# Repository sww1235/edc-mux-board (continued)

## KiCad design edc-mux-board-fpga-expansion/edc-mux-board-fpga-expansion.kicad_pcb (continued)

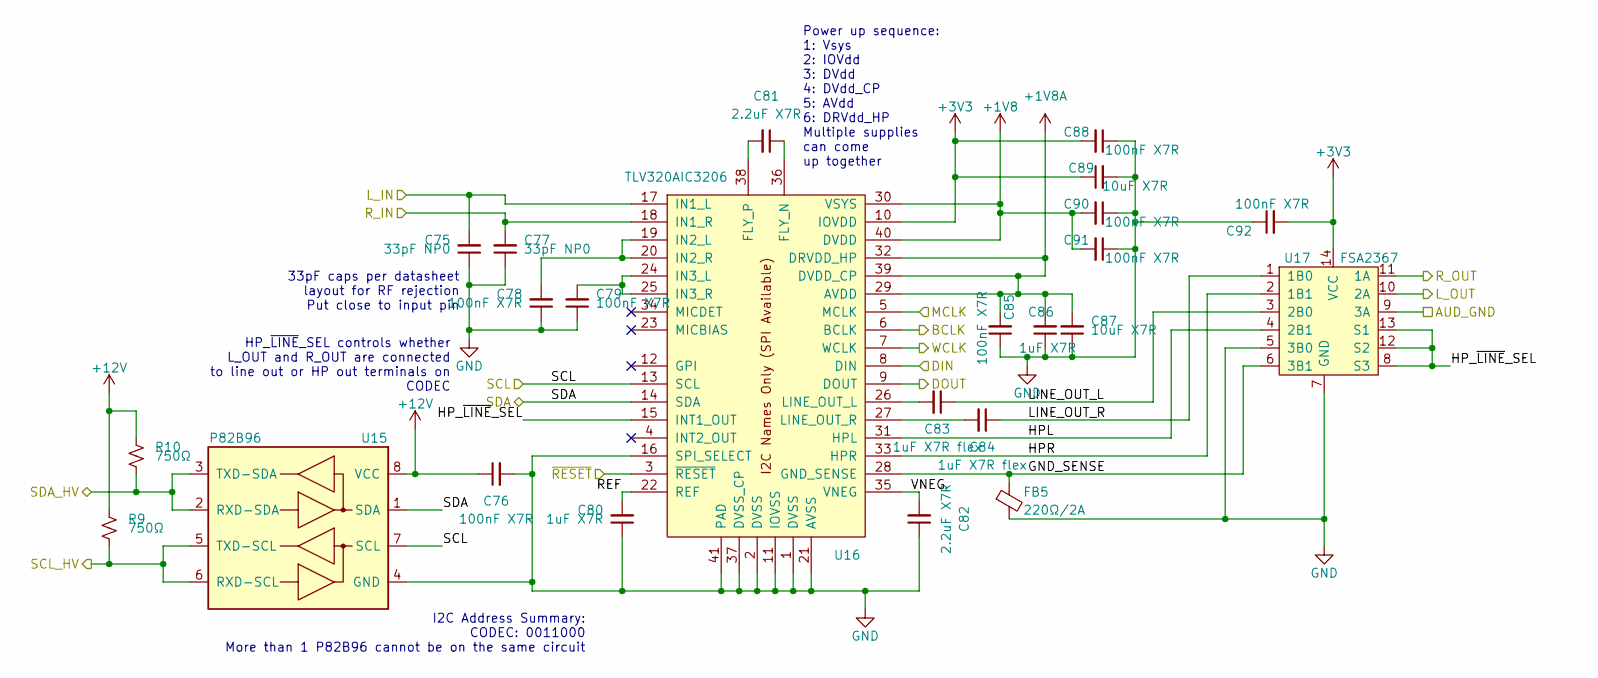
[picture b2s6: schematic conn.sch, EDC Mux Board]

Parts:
C3, C5: 33pF NP0; C_0402_1005Metric; Manufacturers Part Numb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 04023A330FAT2A
C4, C6, C7, C13, C16, C18, C19, C20: 100nF X7R; C_0603_1608Metric; Manufacturers Part Numb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 C0603C104J3RACAUTO
C8, C14: 1uF X7R; C_0603_1608Metric; Manufacturers Part Numb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 CGA3E1X7R1E105K080AC
C9, C10: 2.2uF X7R; C_0805_2012Metric; Manufacturers Part Numb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 CGA4J3X7R1E225K125AB
C11, C12: 1uF X7R flex; C_0805_2012Metric; Manufacturers Part Numb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 C0805X105J3RECAUTO
C15, C17: 10uF X7R; C_1206_3216Metric; Manufacturers Part Numb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 C1206C106J3RACAUTO
FB1: 220Ω/2A; L_0603_1608Metric; Manufacturers Part Numb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 MPZ1608S221A
R1, R2: 750Ω; R_0402_1005Metric
U3: P82B96; TSSOP-8_3x3mm_P0.65mm; Manufacturers Part Numb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 P82B96
U4: TLV320AIC3206; UQFN-40-1EP_5x5mm_P0.4mm_EP3.8x3.8mm_ThermalVias; Manufacturers Part Numb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 TLV320AIC3206
U5: FSA2367; TSSOP-14_4.4x5mm_P0.65mm; Manufacturers Part Numb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 FSA2367MTCX

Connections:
+1V8: C13.2, C14.2, C15.2, C18.2, C19.2, U4.29 (AVDD), U4.30 (VSYS), U4.32 (DRVDD_HP), U4.39 (DVDD_CP), U4.40 (DVDD); also elsewhere on the board
+3V3: C16.2, C17.1, C20.2, U4.10 (IOVDD), U5.14 (VCC); also elsewhere on the board
+12V: C4.1, R1.1, R2.1, U3.8 (VCC); also elsewhere on the board
/Bottom Side Connector Interconnects/BCLK8: U4.6 (BCLK); also elsewhere on the board
/Bottom Side Connector Interconnects/DIN8: U4.8 (DIN); also elsewhere on the board
/Bottom Side Connector Interconnects/DOUT8: U4.9 (DOUT); also elsewhere on the board
/Bottom Side Connector Interconnects/WCLK8: U4.7 (WCLK); also elsewhere on the board
/CODEC interconnection sheet/AUD_GND8: U5.9 (3A); also elsewhere on the board
/CODEC interconnection sheet/Interface - Connector 8/GND_SENSE: FB1.1, U4.28 (GND_SENSE), U5.6 (3B1)
/CODEC interconnection sheet/Interface - Connector 8/HPL: U4.31 (HPL), U5.4 (2B1)
/CODEC interconnection sheet/Interface - Connector 8/HPR: U4.33 (HPR), U5.2 (1B1)
/CODEC interconnection sheet/Interface - Connector 8/HP_~LINE~_SEL: U4.15 (INT1_OUT), U5.8 (S3), U5.12 (S2), U5.13 (S1)
/CODEC interconnection sheet/Interface - Connector 8/LINE_OUT_L: C11.1, U5.3 (2B0)
/CODEC interconnection sheet/Interface - Connector 8/LINE_OUT_R: C12.1, U5.1 (1B0)
/CODEC interconnection sheet/Interface - Connector 8/REF: C8.2, U4.22 (REF)
/CODEC interconnection sheet/Interface - Connector 8/VNEG: C10.2, U4.35 (VNEG)
/CODEC interconnection sheet/L_IN8: C3.2, U4.17 (IN1_L); also elsewhere on the board
/CODEC interconnection sheet/L_OUT8: U5.10 (2A); also elsewhere on the board
/CODEC interconnection sheet/MCLK8: U4.5 (MCLK); also elsewhere on the board
/CODEC interconnection sheet/R_IN8: C5.2, U4.18 (IN1_R); also elsewhere on the board
/CODEC interconnection sheet/R_OUT8: U5.11 (1A); also elsewhere on the board
/CODEC interconnection sheet/SCL8: U3.7 (SCL), U4.13 (SCL); also elsewhere on the board
/CODEC interconnection sheet/SCL_HV8: R1.2, U3.5 (TXD-SCL), U3.6 (RXD-SCL); also elsewhere on the board
/CODEC interconnection sheet/SDA8: U3.1 (SDA), U4.14 (SDA); also elsewhere on the board
/CODEC interconnection sheet/SDA_HV8: R2.2, U3.2 (RXD-SDA), U3.3 (TXD-SDA); also elsewhere on the board
/CODEC interconnection sheet/~RESET~8: U4.3 (~RESET); also elsewhere on the board
GND: C3.1, C4.2, C5.1, C6.1, C7.1, C8.1, C10.1, C13.1, C14.1, C15.1, C16.1, C17.2, C18.1, C19.1, C20.1, FB1.2, U3.4 (GND), U4.1 (DVSS), U4.2 (DVSS), U4.11 (IOVSS), U4.16 (SPI_SELECT), U4.21 (AVSS), U4.37 (DVSS_CP), U4.41 (PAD), U5.5 (3B0), U5.7 (GND); also elsewhere on the board
unnamed: C6.2, U4.19 (IN2_L), U4.20 (IN2_R)
unnamed: C7.2, U4.24 (IN3_L), U4.25 (IN3_R)
unnamed: C9.1, U4.36 (FLY_N)
unnamed: C9.2, U4.38 (FLY_P)
unnamed: C11.2, U4.26 (LINE_OUT_L)
unnamed: C12.2, U4.27 (LINE_OUT_R)

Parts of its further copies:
C21, C23, C39, C41, C57, C59, C75, C77, C93, C95, C111, C113, C129, C131: 33pF NP0; C_0402_1005Metric; Manufacturers Part Numb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 04023A330FAT2A
C22, C24, C25, C31, C34, C36, C37, C38, C40, C42, C43, C49, C52, C54, C55, C56, C58, C60, C61, C67, C70, C72, C73, C74, C76, C78, C79, C85, C88, C90, C91, C92, C94, C96, C97, C103, C106, C108, C109, C110, C112, C114, C115, C121, C124, C126, C127, C128, C130, C132, C133, C139, C142, C144, C145, C146: 100nF X7R; C_0603_1608Metric; Manufacturers Part Numb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 C0603C104J3RACAUTO
C26, C32, C44, C50, C62, C68, C80, C86, C98, C104, C116, C122, C134, C140: 1uF X7R; C_0603_1608Metric; Manufacturers Part Numb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 CGA3E1X7R1E105K080AC
C27, C28, C45, C46, C63, C64, C81, C82, C99, C100, C117, C118, C135, C136: 2.2uF X7R; C_0805_2012Metric; Manufacturers Part Numb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 CGA4J3X7R1E225K125AB
C29, C30, C47, C48, C65, C66, C83, C84, C101, C102, C119, C120, C137, C138: 1uF X7R flex; C_0805_2012Metric; Manufacturers Part Numb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 C0805X105J3RECAUTO
C33, C35, C51, C53, C69, C71, C87, C89, C105, C107, C123, C125, C141, C143: 10uF X7R; C_1206_3216Metric; Manufacturers Part Numb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 C1206C106J3RACAUTO
FB2, FB3, FB4, FB5, FB6, FB7, FB8: 220Ω/2A; L_0603_1608Metric; Manufacturers Part Numb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 MPZ1608S221A
R3, R4, R5, R6, R7, R8, R9, R10, R11, R12, R13, R14, R15, R16: 750Ω; R_0402_1005Metric
U6, U9, U12, U15, U18, U21, U24: P82B96; TSSOP-8_3x3mm_P0.65mm; Manufacturers Part Numb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 P82B96
U7, U10, U13, U16, U19, U22, U25: TLV320AIC3206; UQFN-40-1EP_5x5mm_P0.4mm_EP3.8x3.8mm_ThermalVias; Manufacturers Part Numb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 TLV320AIC3206
U8, U11, U14, U17, U20, U23, U26: FSA2367; TSSOP-14_4.4x5mm_P0.65mm; Manufacturers Part Numb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 FSA2367MTCX

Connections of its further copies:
+1V8: C31.2, C32.2, C33.2, C36.2, C37.2, C49.2, C50.2, C51.2, C54.2, C55.2, C67.2, C68.2, C69.2, C72.2, C73.2, C85.2, C86.2, C87.2, C90.2, C91.2, C103.2, C104.2, C105.2, C108.2, C109.2, C121.2, C122.2, C123.2, C126.2, C127.2, C139.2, C140.2, C141.2, C144.2, C145.2, U7.29 (AVDD), U7.30 (VSYS), U7.32 (DRVDD_HP), U7.39 (DVDD_CP), U7.40 (DVDD), U10.29 (AVDD), U10.30 (VSYS), U10.32 (DRVDD_HP), U10.39 (DVDD_CP), U10.40 (DVDD), U13.29 (AVDD), U13.30 (VSYS), U13.32 (DRVDD_HP), U13.39 (DVDD_CP), U13.40 (DVDD), U16.29 (AVDD), U16.30 (VSYS), U16.32 (DRVDD_HP), U16.39 (DVDD_CP), U16.40 (DVDD), U19.29 (AVDD), U19.30 (VSYS), U19.32 (DRVDD_HP), U19.39 (DVDD_CP), U19.40 (DVDD), U22.29 (AVDD), U22.30 (VSYS), U22.32 (DRVDD_HP), U22.39 (DVDD_CP), U22.40 (DVDD), U25.29 (AVDD), U25.30 (VSYS), U25.32 (DRVDD_HP), U25.39 (DVDD_CP), U25.40 (DVDD); also elsewhere on the board
+3V3: C34.2, C35.1, C38.2, C52.2, C53.1, C56.2, C70.2, C71.1, C74.2, C88.2, C89.1, C92.2, C106.2, C107.1, C110.2, C124.2, C125.1, C128.2, C142.2, C143.1, C146.2, U7.10 (IOVDD), U8.14 (VCC), U10.10 (IOVDD), U11.14 (VCC), U13.10 (IOVDD), U14.14 (VCC), U16.10 (IOVDD), U17.14 (VCC), U19.10 (IOVDD), U20.14 (VCC), U22.10 (IOVDD), U23.14 (VCC), U25.10 (IOVDD), U26.14 (VCC); also elsewhere on the board
+12V: C22.1, C40.1, C58.1, C76.1, C94.1, C112.1, C130.1, R3.1, R4.1, R5.1, R6.1, R7.1, R8.1, R9.1, R10.1, R11.1, R12.1, R13.1, R14.1, R15.1, R16.1, U6.8 (VCC), U9.8 (VCC), U12.8 (VCC), U15.8 (VCC), U18.8 (VCC), U21.8 (VCC), U24.8 (VCC); also elsewhere on the board
/Bottom Side Connector Interconnects/BCLK9: U7.6 (BCLK); also elsewhere on the board
/Bottom Side Connector Interconnects/BCLK10: U10.6 (BCLK); also elsewhere on the board
/Bottom Side Connector Interconnects/BCLK11: U13.6 (BCLK); also elsewhere on the board
/Bottom Side Connector Interconnects/BCLK12: U16.6 (BCLK); also elsewhere on the board
/Bottom Side Connector Interconnects/BCLK13: U19.6 (BCLK); also elsewhere on the board
/Bottom Side Connector Interconnects/BCLK14: U22.6 (BCLK); also elsewhere on the board
/Bottom Side Connector Interconnects/BCLK15: U25.6 (BCLK); also elsewhere on the board
/Bottom Side Connector Interconnects/DIN9: U7.8 (DIN); also elsewhere on the board
/Bottom Side Connector Interconnects/DIN10: U10.8 (DIN); also elsewhere on the board
/Bottom Side Connector Interconnects/DIN11: U13.8 (DIN); also elsewhere on the board
/Bottom Side Connector Interconnects/DIN12: U16.8 (DIN); also elsewhere on the board
/Bottom Side Connector Interconnects/DIN13: U19.8 (DIN); also elsewhere on the board
/Bottom Side Connector Interconnects/DIN14: U22.8 (DIN); also elsewhere on the board
/Bottom Side Connector Interconnects/DIN15: U25.8 (DIN); also elsewhere on the board
/Bottom Side Connector Interconnects/DOUT9: U7.9 (DOUT); also elsewhere on the board
/Bottom Side Connector Interconnects/DOUT10: U10.9 (DOUT); also elsewhere on the board
/Bottom Side Connector Interconnects/DOUT11: U13.9 (DOUT); also elsewhere on the board
/Bottom Side Connector Interconnects/DOUT12: U16.9 (DOUT); also elsewhere on the board
/Bottom Side Connector Interconnects/DOUT13: U19.9 (DOUT); also elsewhere on the board
/Bottom Side Connector Interconnects/DOUT14: U22.9 (DOUT); also elsewhere on the board
/Bottom Side Connector Interconnects/DOUT15: U25.9 (DOUT); also elsewhere on the board
/Bottom Side Connector Interconnects/WCLK9: U7.7 (WCLK); also elsewhere on the board
/Bottom Side Connector Interconnects/WCLK10: U10.7 (WCLK); also elsewhere on the board
/Bottom Side Connector Interconnects/WCLK11: U13.7 (WCLK); also elsewhere on the board
/Bottom Side Connector Interconnects/WCLK12: U16.7 (WCLK); also elsewhere on the board
/Bottom Side Connector Interconnects/WCLK13: U19.7 (WCLK); also elsewhere on the board
/Bottom Side Connector Interconnects/WCLK14: U22.7 (WCLK); also elsewhere on the board
/Bottom Side Connector Interconnects/WCLK15: U25.7 (WCLK); also elsewhere on the board
/CODEC interconnection sheet/AUD_GND9: U8.9 (3A); also elsewhere on the board
/CODEC interconnection sheet/AUD_GND10: U11.9 (3A); also elsewhere on the board
/CODEC interconnection sheet/AUD_GND11: U14.9 (3A); also elsewhere on the board
/CODEC interconnection sheet/AUD_GND12: U17.9 (3A); also elsewhere on the board
/CODEC interconnection sheet/AUD_GND13: U20.9 (3A); also elsewhere on the board
/CODEC interconnection sheet/AUD_GND14: U23.9 (3A); also elsewhere on the board
/CODEC interconnection sheet/AUD_GND15: U26.9 (3A); also elsewhere on the board
/CODEC interconnection sheet/Interface - Connector 9/GND_SENSE: FB2.1, U7.28 (GND_SENSE), U8.6 (3B1)
/CODEC interconnection sheet/Interface - Connector 9/HPL: U7.31 (HPL), U8.4 (2B1)
/CODEC interconnection sheet/Interface - Connector 9/HPR: U7.33 (HPR), U8.2 (1B1)
/CODEC interconnection sheet/Interface - Connector 9/HP_~LINE~_SEL: U7.15 (INT1_OUT), U8.8 (S3), U8.12 (S2), U8.13 (S1)
/CODEC interconnection sheet/Interface - Connector 9/LINE_OUT_L: C29.1, U8.3 (2B0)
/CODEC interconnection sheet/Interface - Connector 9/LINE_OUT_R: C30.1, U8.1 (1B0)
/CODEC interconnection sheet/Interface - Connector 9/REF: C26.2, U7.22 (REF)
/CODEC interconnection sheet/Interface - Connector 9/VNEG: C28.2, U7.35 (VNEG)
/CODEC interconnection sheet/Interface - Connector 10/GND_SENSE: FB3.1, U10.28 (GND_SENSE), U11.6 (3B1)
/CODEC interconnection sheet/Interface - Connector 10/HPL: U10.31 (HPL), U11.4 (2B1)
/CODEC interconnection sheet/Interface - Connector 10/HPR: U10.33 (HPR), U11.2 (1B1)
/CODEC interconnection sheet/Interface - Connector 10/HP_~LINE~_SEL: U10.15 (INT1_OUT), U11.8 (S3), U11.12 (S2), U11.13 (S1)
/CODEC interconnection sheet/Interface - Connector 10/LINE_OUT_L: C47.1, U11.3 (2B0)
/CODEC interconnection sheet/Interface - Connector 10/LINE_OUT_R: C48.1, U11.1 (1B0)
/CODEC interconnection sheet/Interface - Connector 10/REF: C44.2, U10.22 (REF)
/CODEC interconnection sheet/Interface - Connector 10/VNEG: C46.2, U10.35 (VNEG)
/CODEC interconnection sheet/Interface - Connector 11/GND_SENSE: FB4.1, U13.28 (GND_SENSE), U14.6 (3B1)
/CODEC interconnection sheet/Interface - Connector 11/HPL: U13.31 (HPL), U14.4 (2B1)
/CODEC interconnection sheet/Interface - Connector 11/HPR: U13.33 (HPR), U14.2 (1B1)
/CODEC interconnection sheet/Interface - Connector 11/HP_~LINE~_SEL: U13.15 (INT1_OUT), U14.8 (S3), U14.12 (S2), U14.13 (S1)
/CODEC interconnection sheet/Interface - Connector 11/LINE_OUT_L: C65.1, U14.3 (2B0)
/CODEC interconnection sheet/Interface - Connector 11/LINE_OUT_R: C66.1, U14.1 (1B0)
/CODEC interconnection sheet/Interface - Connector 11/REF: C62.2, U13.22 (REF)
/CODEC interconnection sheet/Interface - Connector 11/VNEG: C64.2, U13.35 (VNEG)
/CODEC interconnection sheet/Interface - Connector 12/GND_SENSE: FB5.1, U16.28 (GND_SENSE), U17.6 (3B1)
/CODEC interconnection sheet/Interface - Connector 12/HPL: U16.31 (HPL), U17.4 (2B1)
/CODEC interconnection sheet/Interface - Connector 12/HPR: U16.33 (HPR), U17.2 (1B1)
/CODEC interconnection sheet/Interface - Connector 12/HP_~LINE~_SEL: U16.15 (INT1_OUT), U17.8 (S3), U17.12 (S2), U17.13 (S1)
/CODEC interconnection sheet/Interface - Connector 12/LINE_OUT_L: C83.1, U17.3 (2B0)
/CODEC interconnection sheet/Interface - Connector 12/LINE_OUT_R: C84.1, U17.1 (1B0)
/CODEC interconnection sheet/Interface - Connector 12/REF: C80.2, U16.22 (REF)
/CODEC interconnection sheet/Interface - Connector 12/VNEG: C82.2, U16.35 (VNEG)
/CODEC interconnection sheet/Interface - Connector 13/GND_SENSE: FB6.1, U19.28 (GND_SENSE), U20.6 (3B1)
/CODEC interconnection sheet/Interface - Connector 13/HPL: U19.31 (HPL), U20.4 (2B1)
/CODEC interconnection sheet/Interface - Connector 13/HPR: U19.33 (HPR), U20.2 (1B1)
/CODEC interconnection sheet/Interface - Connector 13/HP_~LINE~_SEL: U19.15 (INT1_OUT), U20.8 (S3), U20.12 (S2), U20.13 (S1)
/CODEC interconnection sheet/Interface - Connector 13/LINE_OUT_L: C101.1, U20.3 (2B0)
/CODEC interconnection sheet/Interface - Connector 13/LINE_OUT_R: C102.1, U20.1 (1B0)
/CODEC interconnection sheet/Interface - Connector 13/REF: C98.2, U19.22 (REF)
/CODEC interconnection sheet/Interface - Connector 13/VNEG: C100.2, U19.35 (VNEG)
/CODEC interconnection sheet/Interface - Connector 14/GND_SENSE: FB7.1, U22.28 (GND_SENSE), U23.6 (3B1)
/CODEC interconnection sheet/Interface - Connector 14/HPL: U22.31 (HPL), U23.4 (2B1)
/CODEC interconnection sheet/Interface - Connector 14/HPR: U22.33 (HPR), U23.2 (1B1)
/CODEC interconnection sheet/Interface - Connector 14/HP_~LINE~_SEL: U22.15 (INT1_OUT), U23.8 (S3), U23.12 (S2), U23.13 (S1)
/CODEC interconnection sheet/Interface - Connector 14/LINE_OUT_L: C119.1, U23.3 (2B0)
/CODEC interconnection sheet/Interface - Connector 14/LINE_OUT_R: C120.1, U23.1 (1B0)
/CODEC interconnection sheet/Interface - Connector 14/REF: C116.2, U22.22 (REF)
/CODEC interconnection sheet/Interface - Connector 14/VNEG: C118.2, U22.35 (VNEG)
/CODEC interconnection sheet/Interface - Connector 15/GND_SENSE: FB8.1, U25.28 (GND_SENSE), U26.6 (3B1)
/CODEC interconnection sheet/Interface - Connector 15/HPL: U25.31 (HPL), U26.4 (2B1)
/CODEC interconnection sheet/Interface - Connector 15/HPR: U25.33 (HPR), U26.2 (1B1)
/CODEC interconnection sheet/Interface - Connector 15/HP_~LINE~_SEL: U25.15 (INT1_OUT), U26.8 (S3), U26.12 (S2), U26.13 (S1)
/CODEC interconnection sheet/Interface - Connector 15/LINE_OUT_L: C137.1, U26.3 (2B0)
/CODEC interconnection sheet/Interface - Connector 15/LINE_OUT_R: C138.1, U26.1 (1B0)
/CODEC interconnection sheet/Interface - Connector 15/REF: C134.2, U25.22 (REF)
/CODEC interconnection sheet/Interface - Connector 15/VNEG: C136.2, U25.35 (VNEG)
/CODEC interconnection sheet/L_IN9: C21.2, U7.17 (IN1_L); also elsewhere on the board
/CODEC interconnection sheet/L_IN10: C39.2, U10.17 (IN1_L); also elsewhere on the board
/CODEC interconnection sheet/L_IN11: C57.2, U13.17 (IN1_L); also elsewhere on the board
/CODEC interconnection sheet/L_IN12: C75.2, U16.17 (IN1_L); also elsewhere on the board
/CODEC interconnection sheet/L_IN13: C93.2, U19.17 (IN1_L); also elsewhere on the board
/CODEC interconnection sheet/L_IN14: C111.2, U22.17 (IN1_L); also elsewhere on the board
/CODEC interconnection sheet/L_IN15: C129.2, U25.17 (IN1_L); also elsewhere on the board
/CODEC interconnection sheet/L_OUT9: U8.10 (2A); also elsewhere on the board
/CODEC interconnection sheet/L_OUT10: U11.10 (2A); also elsewhere on the board
/CODEC interconnection sheet/L_OUT11: U14.10 (2A); also elsewhere on the board
/CODEC interconnection sheet/L_OUT12: U17.10 (2A); also elsewhere on the board
/CODEC interconnection sheet/L_OUT13: U20.10 (2A); also elsewhere on the board
/CODEC interconnection sheet/L_OUT14: U23.10 (2A); also elsewhere on the board
/CODEC interconnection sheet/L_OUT15: U26.10 (2A); also elsewhere on the board
/CODEC interconnection sheet/MCLK9: U7.5 (MCLK); also elsewhere on the board
/CODEC interconnection sheet/MCLK10: U10.5 (MCLK); also elsewhere on the board
/CODEC interconnection sheet/MCLK11: U13.5 (MCLK); also elsewhere on the board
/CODEC interconnection sheet/MCLK12: U16.5 (MCLK); also elsewhere on the board
/CODEC interconnection sheet/MCLK13: U19.5 (MCLK); also elsewhere on the board
/CODEC interconnection sheet/MCLK14: U22.5 (MCLK); also elsewhere on the board
/CODEC interconnection sheet/MCLK15: U25.5 (MCLK); also elsewhere on the board
/CODEC interconnection sheet/R_IN9: C23.2, U7.18 (IN1_R); also elsewhere on the board
/CODEC interconnection sheet/R_IN10: C41.2, U10.18 (IN1_R); also elsewhere on the board
/CODEC interconnection sheet/R_IN11: C59.2, U13.18 (IN1_R); also elsewhere on the board
/CODEC interconnection sheet/R_IN12: C77.2, U16.18 (IN1_R); also elsewhere on the board
/CODEC interconnection sheet/R_IN13: C95.2, U19.18 (IN1_R); also elsewhere on the board
/CODEC interconnection sheet/R_IN14: C113.2, U22.18 (IN1_R); also elsewhere on the board
/CODEC interconnection sheet/R_IN15: C131.2, U25.18 (IN1_R); also elsewhere on the board
/CODEC interconnection sheet/R_OUT9: U8.11 (1A); also elsewhere on the board
/CODEC interconnection sheet/R_OUT10: U11.11 (1A); also elsewhere on the board
/CODEC interconnection sheet/R_OUT11: U14.11 (1A); also elsewhere on the board
/CODEC interconnection sheet/R_OUT12: U17.11 (1A); also elsewhere on the board
/CODEC interconnection sheet/R_OUT13: U20.11 (1A); also elsewhere on the board
/CODEC interconnection sheet/R_OUT14: U23.11 (1A); also elsewhere on the board
/CODEC interconnection sheet/R_OUT15: U26.11 (1A); also elsewhere on the board
/CODEC interconnection sheet/SCL9: U6.7 (SCL), U7.13 (SCL); also elsewhere on the board
/CODEC interconnection sheet/SCL10: U9.7 (SCL), U10.13 (SCL); also elsewhere on the board
/CODEC interconnection sheet/SCL11: U12.7 (SCL), U13.13 (SCL); also elsewhere on the board
/CODEC interconnection sheet/SCL12: U15.7 (SCL), U16.13 (SCL); also elsewhere on the board
/CODEC interconnection sheet/SCL13: U18.7 (SCL), U19.13 (SCL); also elsewhere on the board
/CODEC interconnection sheet/SCL14: U21.7 (SCL), U22.13 (SCL); also elsewhere on the board
/CODEC interconnection sheet/SCL15: U24.7 (SCL), U25.13 (SCL); also elsewhere on the board
/CODEC interconnection sheet/SCL_HV9: R3.2, U6.5 (TXD-SCL), U6.6 (RXD-SCL); also elsewhere on the board
/CODEC interconnection sheet/SCL_HV10: R5.2, U9.5 (TXD-SCL), U9.6 (RXD-SCL); also elsewhere on the board
/CODEC interconnection sheet/SCL_HV11: R7.2, U12.5 (TXD-SCL), U12.6 (RXD-SCL); also elsewhere on the board
/CODEC interconnection sheet/SCL_HV12: R9.2, U15.5 (TXD-SCL), U15.6 (RXD-SCL); also elsewhere on the board
/CODEC interconnection sheet/SCL_HV13: R11.2, U18.5 (TXD-SCL), U18.6 (RXD-SCL); also elsewhere on the board
/CODEC interconnection sheet/SCL_HV14: R13.2, U21.5 (TXD-SCL), U21.6 (RXD-SCL); also elsewhere on the board
/CODEC interconnection sheet/SCL_HV15: R15.2, U24.5 (TXD-SCL), U24.6 (RXD-SCL); also elsewhere on the board
/CODEC interconnection sheet/SDA9: U6.1 (SDA), U7.14 (SDA); also elsewhere on the board
/CODEC interconnection sheet/SDA10: U9.1 (SDA), U10.14 (SDA); also elsewhere on the board
/CODEC interconnection sheet/SDA11: U12.1 (SDA), U13.14 (SDA); also elsewhere on the board
/CODEC interconnection sheet/SDA12: U15.1 (SDA), U16.14 (SDA); also elsewhere on the board
/CODEC interconnection sheet/SDA13: U18.1 (SDA), U19.14 (SDA); also elsewhere on the board
/CODEC interconnection sheet/SDA14: U21.1 (SDA), U22.14 (SDA); also elsewhere on the board
/CODEC interconnection sheet/SDA15: U24.1 (SDA), U25.14 (SDA); also elsewhere on the board
/CODEC interconnection sheet/SDA_HV9: R4.2, U6.2 (RXD-SDA), U6.3 (TXD-SDA); also elsewhere on the board
/CODEC interconnection sheet/SDA_HV10: R6.2, U9.2 (RXD-SDA), U9.3 (TXD-SDA); also elsewhere on the board
/CODEC interconnection sheet/SDA_HV11: R8.2, U12.2 (RXD-SDA), U12.3 (TXD-SDA); also elsewhere on the board
/CODEC interconnection sheet/SDA_HV12: R10.2, U15.2 (RXD-SDA), U15.3 (TXD-SDA); also elsewhere on the board
/CODEC interconnection sheet/SDA_HV13: R12.2, U18.2 (RXD-SDA), U18.3 (TXD-SDA); also elsewhere on the board
/CODEC interconnection sheet/SDA_HV14: R14.2, U21.2 (RXD-SDA), U21.3 (TXD-SDA); also elsewhere on the board
/CODEC interconnection sheet/SDA_HV15: R16.2, U24.2 (RXD-SDA), U24.3 (TXD-SDA); also elsewhere on the board
/CODEC interconnection sheet/~RESET~9: U7.3 (~RESET); also elsewhere on the board
/CODEC interconnection sheet/~RESET~10: U10.3 (~RESET); also elsewhere on the board
/CODEC interconnection sheet/~RESET~11: U13.3 (~RESET); also elsewhere on the board
/CODEC interconnection sheet/~RESET~12: U16.3 (~RESET); also elsewhere on the board
/CODEC interconnection sheet/~RESET~13: U19.3 (~RESET); also elsewhere on the board
/CODEC interconnection sheet/~RESET~14: U22.3 (~RESET); also elsewhere on the board
/CODEC interconnection sheet/~RESET~15: U25.3 (~RESET); also elsewhere on the board
GND: C21.1, C22.2, C23.1, C24.1, C25.1, C26.1, C28.1, C31.1, C32.1, C33.1, C34.1, C35.2, C36.1, C37.1, C38.1, C39.1, C40.2, C41.1, C42.1, C43.1, C44.1, C46.1, C49.1, C50.1, C51.1, C52.1, C53.2, C54.1, C55.1, C56.1, C57.1, C58.2, C59.1, C60.1, C61.1, C62.1, C64.1, C67.1, C68.1, C69.1, C70.1, C71.2, C72.1, C73.1, C74.1, C75.1, C76.2, C77.1, C78.1, C79.1, C80.1, C82.1, C85.1, C86.1, C87.1, C88.1, C89.2, C90.1, C91.1, C92.1, C93.1, C94.2, C95.1, C96.1, C97.1, C98.1, C100.1, C103.1, C104.1, C105.1, C106.1, C107.2, C108.1, C109.1, C110.1, C111.1, C112.2, C113.1, C114.1, C115.1, C116.1, C118.1, C121.1, C122.1, C123.1, C124.1, C125.2, C126.1, C127.1, C128.1, C129.1, C130.2, C131.1, C132.1, C133.1, C134.1, C136.1, C139.1, C140.1, C141.1, C142.1, C143.2, C144.1, C145.1, C146.1, FB2.2, FB3.2, FB4.2, FB5.2, FB6.2, FB7.2, FB8.2, U6.4 (GND), U7.1 (DVSS), U7.2 (DVSS), U7.11 (IOVSS), U7.16 (SPI_SELECT), U7.21 (AVSS), U7.37 (DVSS_CP), U7.41 (PAD), U8.5 (3B0), U8.7 (GND), U9.4 (GND), U10.1 (DVSS), U10.2 (DVSS), U10.11 (IOVSS), U10.16 (SPI_SELECT), U10.21 (AVSS), U10.37 (DVSS_CP), U10.41 (PAD), U11.5 (3B0), U11.7 (GND), U12.4 (GND), U13.1 (DVSS), U13.2 (DVSS), U13.11 (IOVSS), U13.16 (SPI_SELECT), U13.21 (AVSS), U13.37 (DVSS_CP), U13.41 (PAD), U14.5 (3B0), U14.7 (GND), U15.4 (GND), U16.1 (DVSS), U16.2 (DVSS), U16.11 (IOVSS), U16.16 (SPI_SELECT), U16.21 (AVSS), U16.37 (DVSS_CP), U16.41 (PAD), U17.5 (3B0), U17.7 (GND), U18.4 (GND), U19.1 (DVSS), U19.2 (DVSS), U19.11 (IOVSS), U19.16 (SPI_SELECT), U19.21 (AVSS), U19.37 (DVSS_CP), U19.41 (PAD), U20.5 (3B0), U20.7 (GND), U21.4 (GND), U22.1 (DVSS), U22.2 (DVSS), U22.11 (IOVSS), U22.16 (SPI_SELECT), U22.21 (AVSS), U22.37 (DVSS_CP), U22.41 (PAD), U23.5 (3B0), U23.7 (GND), U24.4 (GND), U25.1 (DVSS), U25.2 (DVSS), U25.11 (IOVSS), U25.16 (SPI_SELECT), U25.21 (AVSS), U25.37 (DVSS_CP), U25.41 (PAD), U26.5 (3B0), U26.7 (GND); also elsewhere on the board
unnamed: C24.2, U7.19 (IN2_L), U7.20 (IN2_R)
unnamed: C25.2, U7.24 (IN3_L), U7.25 (IN3_R)
unnamed: C27.1, U7.36 (FLY_N)
unnamed: C27.2, U7.38 (FLY_P)
unnamed: C29.2, U7.26 (LINE_OUT_L)
unnamed: C30.2, U7.27 (LINE_OUT_R)
unnamed: C42.2, U10.19 (IN2_L), U10.20 (IN2_R)
unnamed: C43.2, U10.24 (IN3_L), U10.25 (IN3_R)
unnamed: C45.1, U10.36 (FLY_N)
unnamed: C45.2, U10.38 (FLY_P)
unnamed: C47.2, U10.26 (LINE_OUT_L)
unnamed: C48.2, U10.27 (LINE_OUT_R)
unnamed: C60.2, U13.19 (IN2_L), U13.20 (IN2_R)
unnamed: C61.2, U13.24 (IN3_L), U13.25 (IN3_R)
unnamed: C63.1, U13.36 (FLY_N)
unnamed: C63.2, U13.38 (FLY_P)
unnamed: C65.2, U13.26 (LINE_OUT_L)
unnamed: C66.2, U13.27 (LINE_OUT_R)
unnamed: C78.2, U16.19 (IN2_L), U16.20 (IN2_R)
unnamed: C79.2, U16.24 (IN3_L), U16.25 (IN3_R)
unnamed: C81.1, U16.36 (FLY_N)
unnamed: C81.2, U16.38 (FLY_P)
unnamed: C83.2, U16.26 (LINE_OUT_L)
unnamed: C84.2, U16.27 (LINE_OUT_R)
unnamed: C96.2, U19.19 (IN2_L), U19.20 (IN2_R)
unnamed: C97.2, U19.24 (IN3_L), U19.25 (IN3_R)
unnamed: C99.1, U19.36 (FLY_N)
unnamed: C99.2, U19.38 (FLY_P)
unnamed: C101.2, U19.26 (LINE_OUT_L)
unnamed: C102.2, U19.27 (LINE_OUT_R)
unnamed: C114.2, U22.19 (IN2_L), U22.20 (IN2_R)
unnamed: C115.2, U22.24 (IN3_L), U22.25 (IN3_R)
unnamed: C117.1, U22.36 (FLY_N)
unnamed: C117.2, U22.38 (FLY_P)
unnamed: C119.2, U22.26 (LINE_OUT_L)
unnamed: C120.2, U22.27 (LINE_OUT_R)
unnamed: C132.2, U25.19 (IN2_L), U25.20 (IN2_R)
unnamed: C133.2, U25.24 (IN3_L), U25.25 (IN3_R)
unnamed: C135.1, U25.36 (FLY_N)
unnamed: C135.2, U25.38 (FLY_P)
unnamed: C137.2, U25.26 (LINE_OUT_L)
unnamed: C138.2, U25.27 (LINE_OUT_R)

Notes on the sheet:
33pF caps per datasheet layout for RF rejection Put close to input pin
Power up sequence: 1: Vsys 2: IOVdd 3: DVdd 4: DVdd_CP 5: AVdd 6: DRVdd_HP Multiple supplies can come up together
HP_~LINE~_SEL controls whether L_OUT and R_OUT are connected to line out or HP out terminals on CODEC
I2C Address Summary: CODEC: 0011000 More than 1 P82B96 cannot be on the same circuit

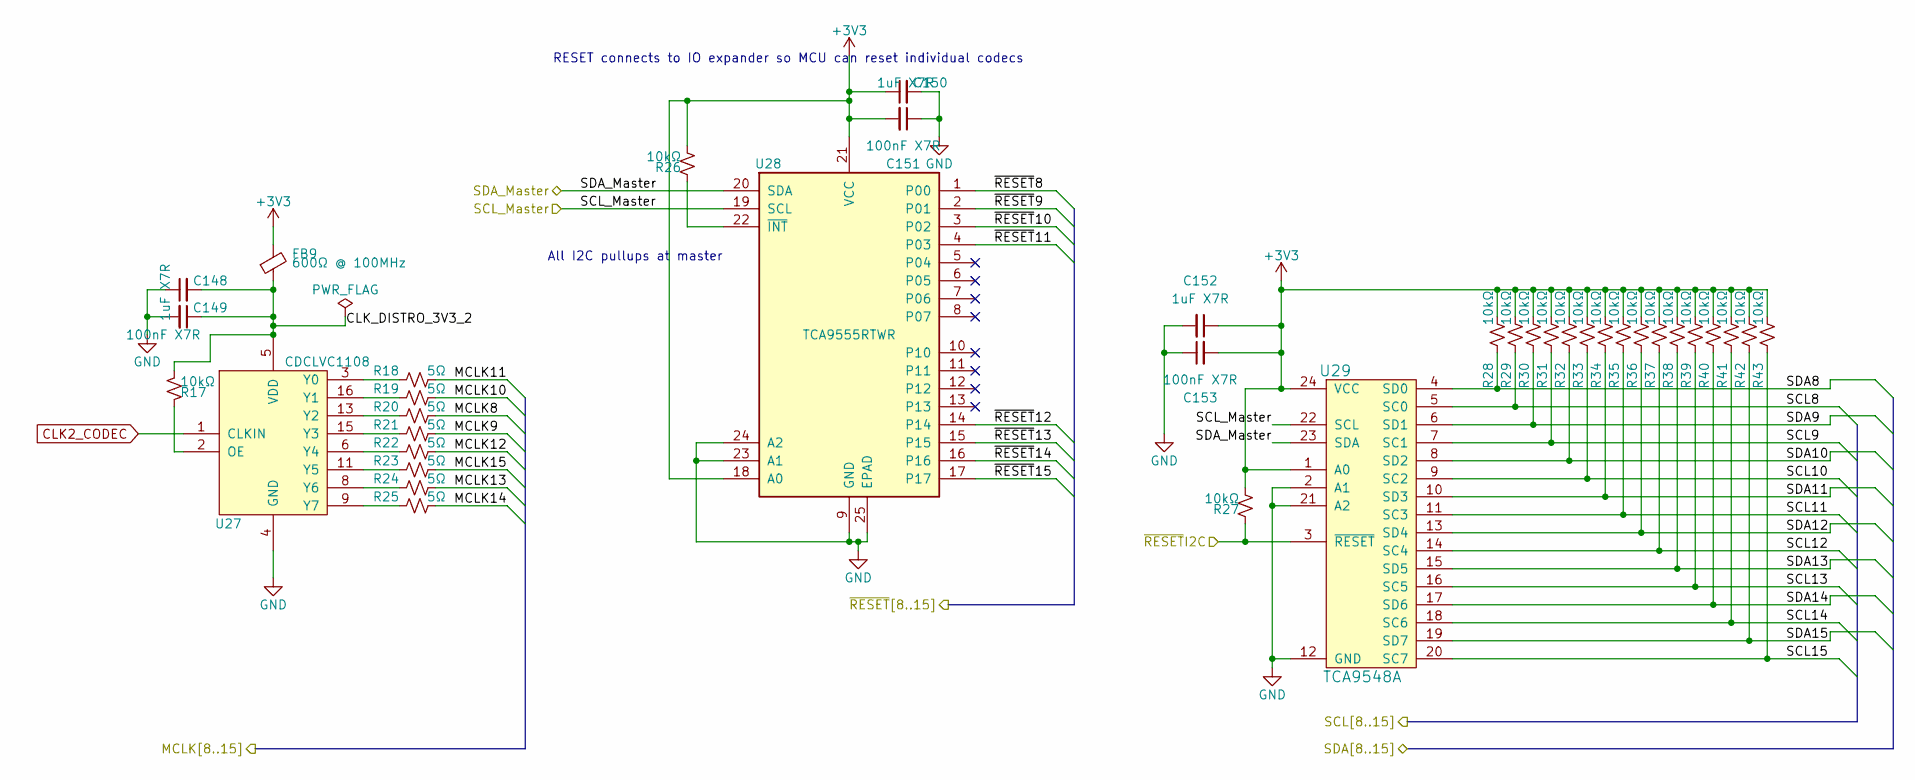
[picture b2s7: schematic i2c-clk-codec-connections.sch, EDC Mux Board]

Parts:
C148, C150, C152: 1uF X7R; C_0603_1608Metric; Manufacturers Part Numb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 CGA3E1X7R1E105K080AC
C149, C151, C153: 100nF X7R; C_0603_1608Metric; Manufacturers Part Numb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 C0603C104J3RACAUTO
FB9: 600Ω @ 100MHz; L_0805_2012Metric; Manufacturers Part Numb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 BLM21AG601SZ1D
R17, R26, R27, R28, R29, R30, R31, R32, R33, R34, R35, R36, R37, R38, R39, R40, R41, R42, R43: 10kΩ; R_0402_1005Metric
R18, R19, R20, R21, R22, R23, R24, R25: 5Ω; R_0402_1005Metric
U27: CDCLVC1108; TSSOP-16_4.4x5mm_P0.65mm; Manufacturers Part Numb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 CDCLVC1108
U28: TCA9555RTWR; QFN-24-1EP_4x4mm_P0.5mm_EP2.6x2.6mm_ThermalVias; Manufacturers Part Numb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 TCA9555
U29: TCA9548A; TSSOP-24_4.4x7.8mm_P0.65mm; Manufacturers Part Numb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 TCA9548

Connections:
+3V3: C150.1, C151.2, C152.1, C153.2, FB9.2, R26.2, R27.2, R28.2, R29.2, R30.2, R31.2, R32.2, R33.2, R34.2, R35.2, R36.2, R37.2, R38.2, R39.2, R40.2, R41.2, R42.2, R43.2, U28.18 (A0), U28.21 (VCC), U29.1 (A0), U29.24 (VCC); also elsewhere on the board
/CODEC interconnection sheet/Connections for MCLK and I2C Multiplexed Lines/CLK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: C148.2, C149.1, FB9.1, R17.2, U27.5 (VDD), U27.10 (VDD), U27.14 (VDD)
/CODEC interconnection sheet/MCLK8: R20.1; also elsewhere on the board
/CODEC interconnection sheet/MCLK9: R21.1; also elsewhere on the board
/CODEC interconnection sheet/MCLK10: R19.1; also elsewhere on the board
/CODEC interconnection sheet/MCLK11: R18.1; also elsewhere on the board
/CODEC interconnection sheet/MCLK12: R22.1; also elsewhere on the board
/CODEC interconnection sheet/MCLK13: R24.1; also elsewhere on the board
/CODEC interconnection sheet/MCLK14: R25.1; also elsewhere on the board
/CODEC interconnection sheet/MCLK15: R23.1; also elsewhere on the board
/CODEC interconnection sheet/SCL8: R29.1, U29.5 (SC0); also elsewhere on the board
/CODEC interconnection sheet/SCL9: R31.1, U29.7 (SC1); also elsewhere on the board
/CODEC interconnection sheet/SCL10: R33.1, U29.9 (SC2); also elsewhere on the board
/CODEC interconnection sheet/SCL11: R35.1, U29.11 (SC3); also elsewhere on the board
/CODEC interconnection sheet/SCL12: R37.1, U29.14 (SC4); also elsewhere on the board
/CODEC interconnection sheet/SCL13: R39.1, U29.16 (SC5); also elsewhere on the board
/CODEC interconnection sheet/SCL14: R41.1, U29.18 (SC6); also elsewhere on the board
/CODEC interconnection sheet/SCL15: R43.1, U29.20 (SC7); also elsewhere on the board
/CODEC interconnection sheet/SDA8: R28.1, U29.4 (SD0); also elsewhere on the board
/CODEC interconnection sheet/SDA9: R30.1, U29.6 (SD1); also elsewhere on the board
/CODEC interconnection sheet/SDA10: R32.1, U29.8 (SD2); also elsewhere on the board
/CODEC interconnection sheet/SDA11: R34.1, U29.10 (SD3); also elsewhere on the board
/CODEC interconnection sheet/SDA12: R36.1, U29.13 (SD4); also elsewhere on the board
/CODEC interconnection sheet/SDA13: R38.1, U29.15 (SD5); also elsewhere on the board
/CODEC interconnection sheet/SDA14: R40.1, U29.17 (SD6); also elsewhere on the board
/CODEC interconnection sheet/SDA15: R42.1, U29.19 (SD7); also elsewhere on the board
/CODEC interconnection sheet/~RESET~8: U28.1 (P00); also elsewhere on the board
/CODEC interconnection sheet/~RESET~9: U28.2 (P01); also elsewhere on the board
/CODEC interconnection sheet/~RESET~10: U28.3 (P02); also elsewhere on the board
/CODEC interconnection sheet/~RESET~11: U28.4 (P03); also elsewhere on the board
/CODEC interconnection sheet/~RESET~12: U28.14; also elsewhere on the board
/CODEC interconnection sheet/~RESET~13: U28.15; also elsewhere on the board
/CODEC interconnection sheet/~RESET~14: U28.16; also elsewhere on the board
/CODEC interconnection sheet/~RESET~15: U28.17; also elsewhere on the board
/SCL: U28.19 (SCL), U29.22 (SCL); also elsewhere on the board
/SDA: U28.20 (SDA), U29.23 (SDA); also elsewhere on the board
/~RESET~I2C: R27.1, U29.3 (~RESET); also elsewhere on the board
CLK2_CODEC: U27.1 (CLKIN); also elsewhere on the board
GND: C148.1, C149.2, C150.2, C151.1, C152.2, C153.1, U27.4 (GND), U27.7 (GND), U27.12 (GND), U28.9 (GND), U28.23 (A1), U28.24 (A2), U28.25 (EPAD), U29.2 (A1), U29.12 (GND), U29.21 (A2); also elsewhere on the board
unnamed: R17.1, U27.2 (OE)
unnamed: R18.2, U27.3 (Y0)
unnamed: R19.2, U27.16 (Y1)
unnamed: R20.2, U27.13 (Y2)
unnamed: R21.2, U27.15 (Y3)
unnamed: R22.2, U27.6 (Y4)
unnamed: R23.2, U27.11 (Y5)
unnamed: R24.2, U27.8 (Y6)
unnamed: R25.2, U27.9 (Y7)
unnamed: R26.1, U28.22 (~INT)

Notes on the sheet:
RESET connects to IO expander so MCU can reset individual codecs
All I2C pullups at master

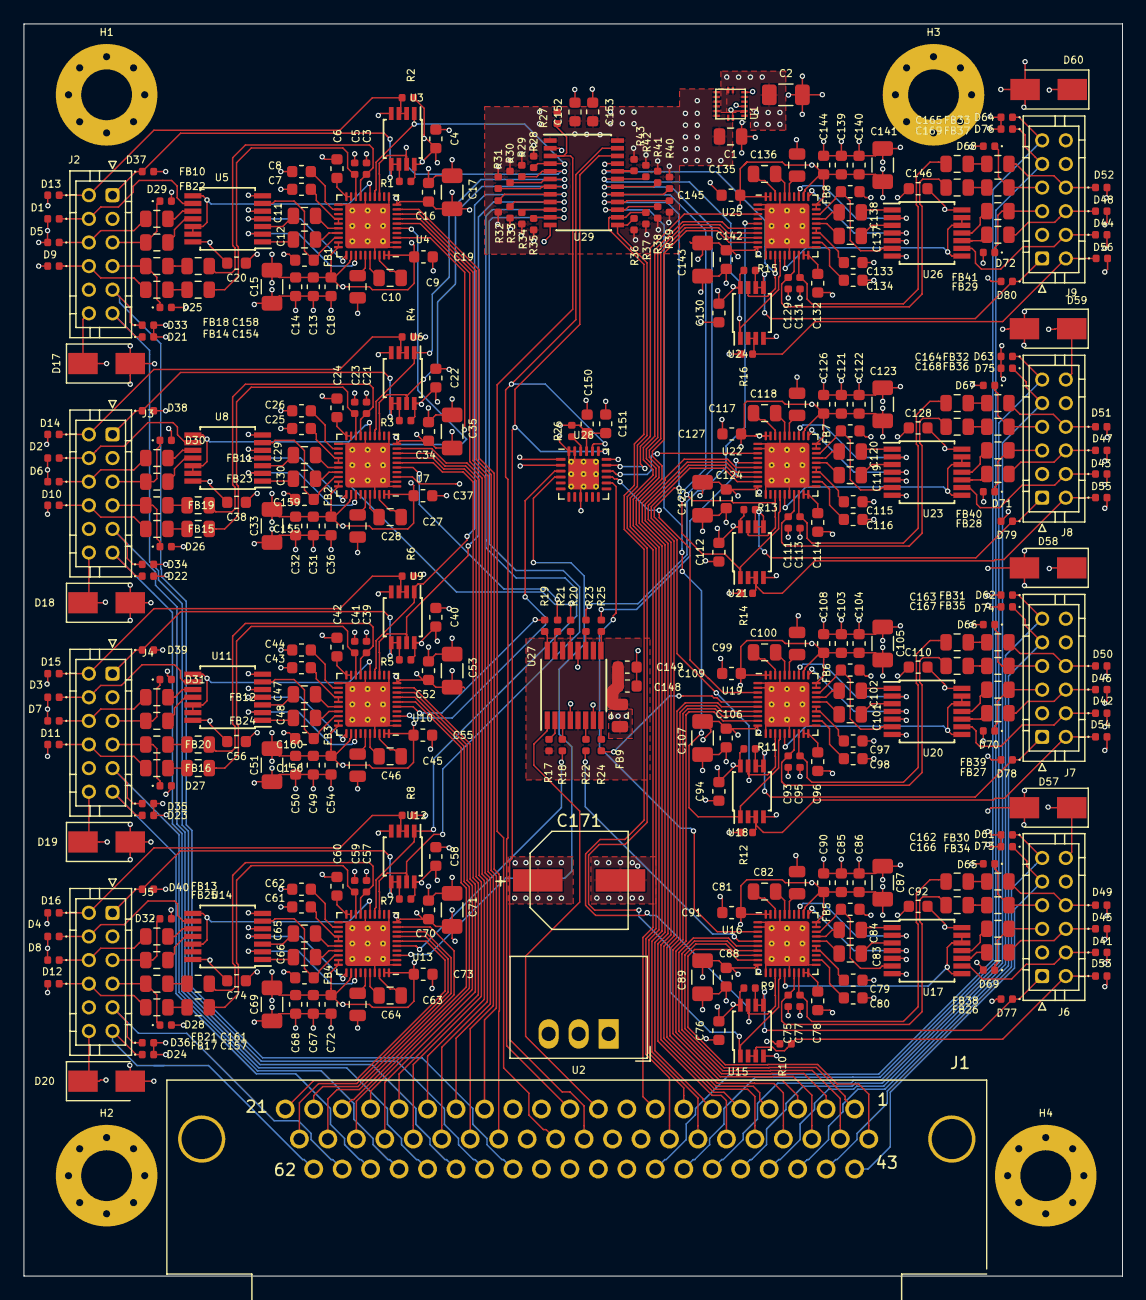
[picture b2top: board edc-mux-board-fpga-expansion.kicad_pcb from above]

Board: 4 copper layers, 93.0 x 106.0 mm, 375 parts (0 on the bottom side), 315 nets.
